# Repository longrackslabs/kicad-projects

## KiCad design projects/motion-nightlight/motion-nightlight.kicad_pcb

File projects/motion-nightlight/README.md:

# Motion Nightlight

Motion-activated nightlight built into a Nest Protect housing. ESP32 firmware, custom PCB, 3D printed enclosure and diffuser.

## Related files

| What | Where |
|------|-------|
| Design artifacts (DIYLC, FreeCAD, STLs, docs) | `Dropbox/Projects/Nest DIY Nightlight/` |
| Firmware | `~/src/platformio-projects/nest_night_light` |

---

## TODO

### PCB Changes

- [ ] Remote LDR — 2-pin JST header instead of THT so it can be positioned anywhere
- [ ] Right-angle JST on J1 and LED1
- [ ] Populate all MPNs in KiCad — needed for AI design review to catch pinout issues
- [ ] Fix C3 symbol — non-polarized ceramic
- [ ] Fix U2 lib_id — 74HC08 not 74LS08
- [ ] Add 47-100Ω resistor between U1 pin 10 and D1 anode
- [ ] Add Rev B silkscreen marking
- [ ] Fix RV1/RV2 3D model absolute paths

### Power

- [ ] Build single supply pigtail — splits one 5V to both V_LED+ and V_CONTROL on J1

### Enclosure

- [ ] Custom enclosure in FreeCAD — proper LED and LDR positioning
- [ ] Custom diffuser — Nest lens doesn't align with custom LED positions
- [ ] Access holes for RV1/RV2 trim pot adjustment

### Assembly

- [ ] First hot air reflow attempt with SAG-55 and Chipquik paste
- [ ] Build second board using incremental gate plan

### Stretch

- [ ] Replace discrete logic with ATtiny for more flexibility
- [ ] PWM dimming on Q2
- [ ] Battery level indicator

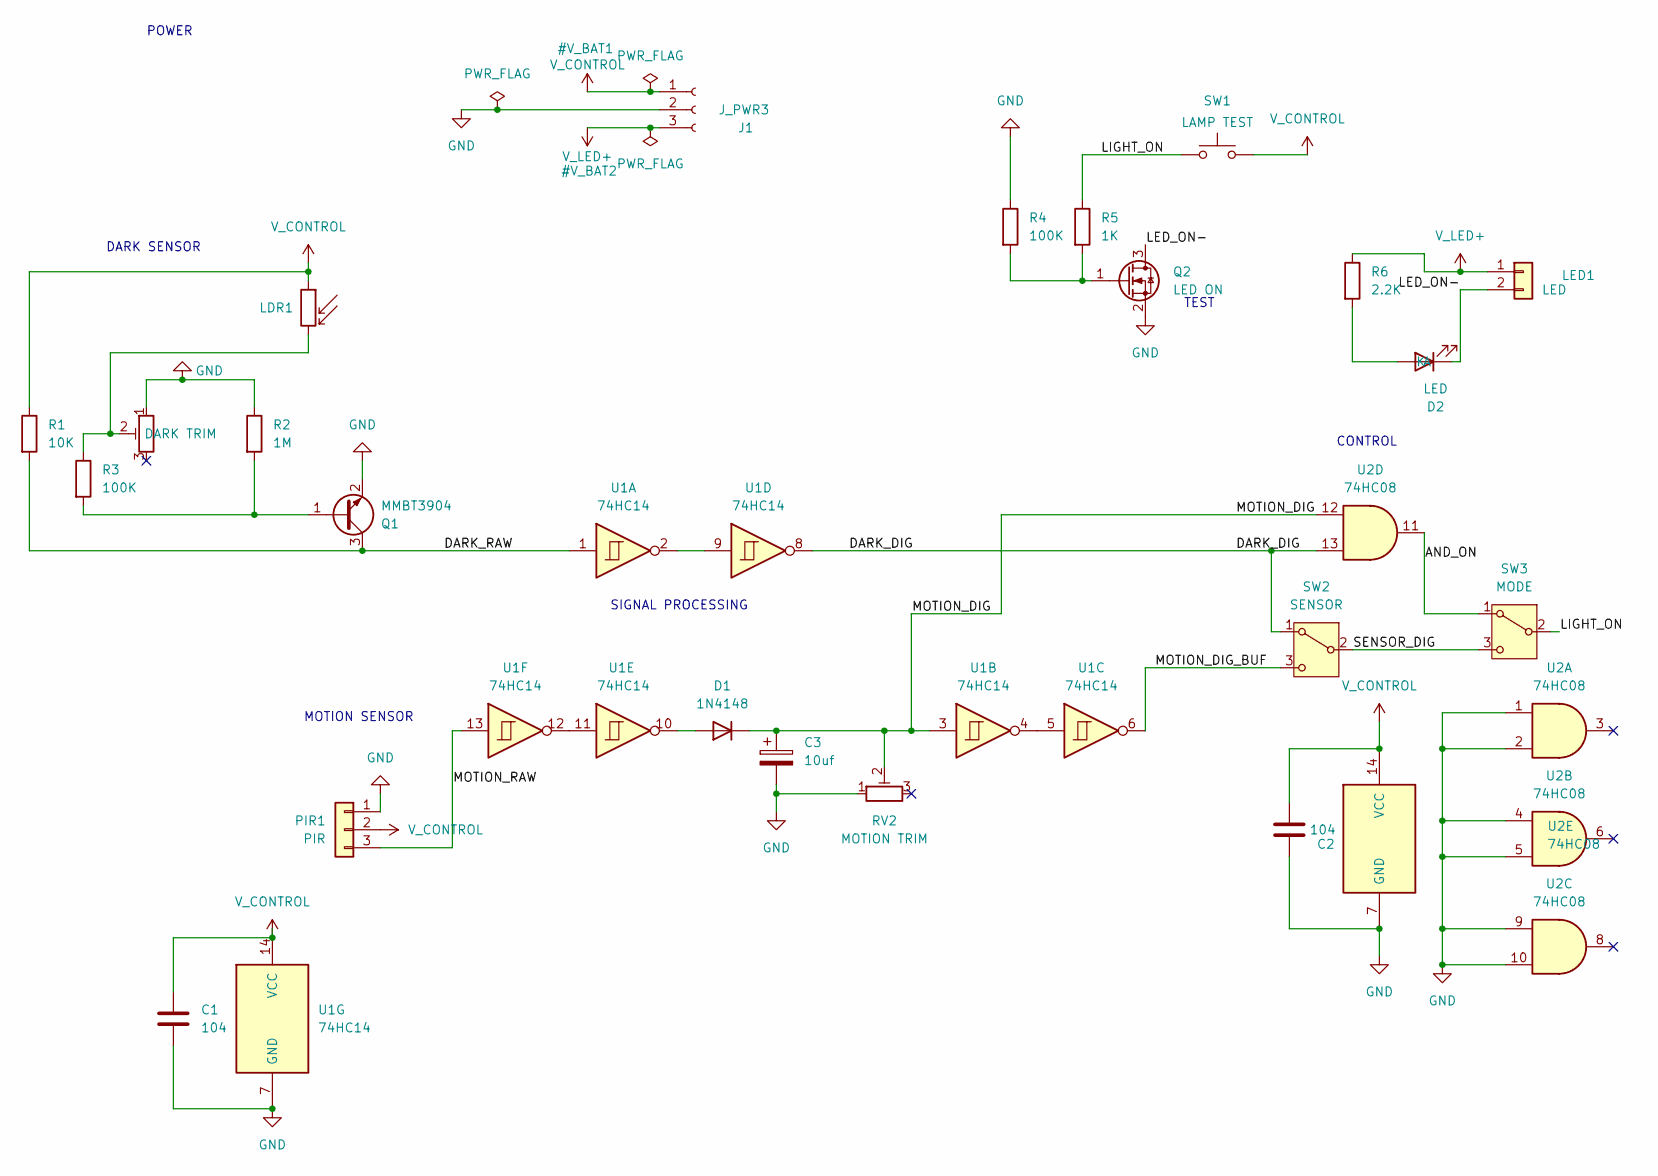
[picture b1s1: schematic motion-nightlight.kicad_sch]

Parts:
C1, C2: 104; C_0805_2012Metric_Pad1.18x1.45mm_HandSolder
C3: 10uf; C_0805_2012Metric_Pad1.18x1.45mm_HandSolder
D1: 1N4148; D_SOD-123
D2: LED; LED_0805_2012Metric
J1: J_PWR3; JST_XH_B3B-XH-A_1x03_P2.50mm_Vertical
LDR1: R_Photo; R_Axial_DIN0207_L6.3mm_D2.5mm_P7.62mm_Horizontal
LED1: LED; JST_XH_B2B-XH-A_1x02_P2.50mm_Vertical
PIR1: PIR; FanPinHeader_1x03_P2.54mm_Vertical
Q1: MMBT3904; SOT-23
Q2: LED ON; SOT-23
R1: 10K; R_0805_2012Metric_Pad1.20x1.40mm_HandSolder
R2: 1M; R_0805_2012Metric_Pad1.20x1.40mm_HandSolder
R3, R4: 100K; R_0805_2012Metric_Pad1.20x1.40mm_HandSolder
R5: 1K; R_0805_2012Metric_Pad1.20x1.40mm_HandSolder
R6: 2.2K; R_0805_2012Metric_Pad1.20x1.40mm_HandSolder
RV1: DARK TRIM; Potentiometer_Bourns_TC33X_Vertical
RV2: MOTION TRIM; Potentiometer_Bourns_TC33X_Vertical
SW1: LAMP TEST; SW_PUSH_6mm_H5mm
SW2: SENSOR; SW_SPDT_PCM12
SW3: MODE; SW_SPDT_PCM12
U1: 74HC14; SOIC-14_3.9x8.7mm_P1.27mm
U2: 74HC08; SOIC-14_3.9x8.7mm_P1.27mm

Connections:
/AND_ON: SW3.1 (A), U2.11
/DARK_DIG: SW2.1 (A), U1.8, U2.13
/DARK_RAW: Q1.3 (C), R1.2, U1.1
/LED_ON-: D2.1 (K), LED1.2, Q2.3 (D)
/LIGHT_ON: R5.1, SW1.1, SW3.2 (B)
/MOTION_DIG: C3.1, D1.1 (K), RV2.2, U1.3, U2.12
/MOTION_DIG_BUF: SW2.3 (C), U1.6
/MOTION_RAW: PIR1.3, U1.13
/SENSOR_DIG: SW2.2 (B), SW3.3 (C)
GND: C1.2, C2.2, C3.2, J1.2, PIR1.1, Q1.2 (E), Q2.2 (S), R2.1, R4.1, RV1.1, RV2.1, U1.7 (GND), U2.1, U2.2, U2.4, U2.5, U2.7 (GND), U2.9, U2.10
unnamed: D1.2 (A), U1.10
unnamed: D2.2 (A), R6.2
unnamed: LDR1.2, R3.1, RV1.2
unnamed: Q1.1 (B), R2.2, R3.2
unnamed: Q2.1 (G), R4.2, R5.2
unnamed: U1.2, U1.9
unnamed: U1.4, U1.5
unnamed: U1.11, U1.12
V_CONTROL: C1.1, C2.1, J1.1, LDR1.1, PIR1.2, R1.1, SW1.2, U1.14 (VCC), U2.14 (VCC)
V_LED+: J1.3, LED1.1, R6.1

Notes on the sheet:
POWER
DARK SENSOR
SIGNAL PROCESSING
MOTION SENSOR
CONTROL
TEST

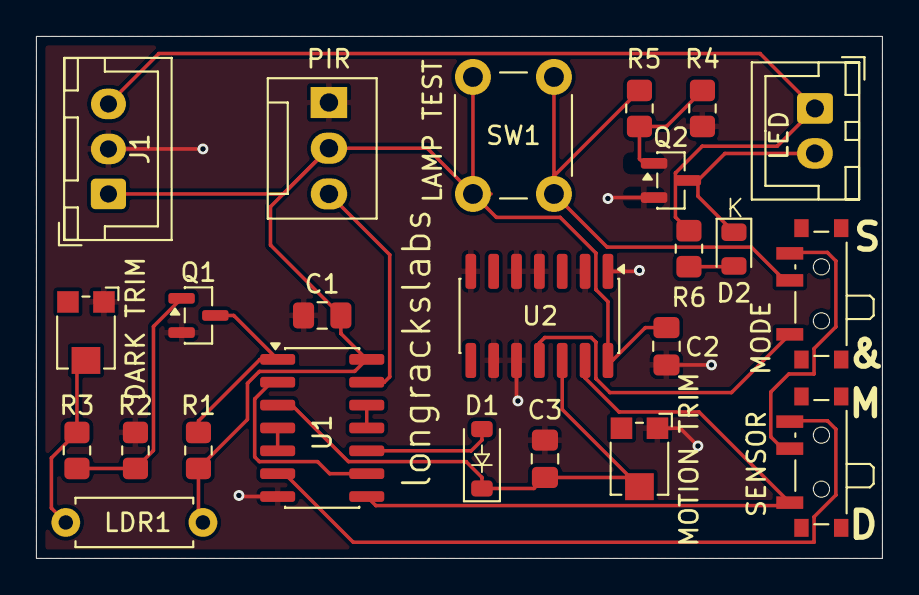
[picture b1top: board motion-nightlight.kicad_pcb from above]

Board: 2 copper layers, 47.0 x 29.0 mm, 24 parts (0 on the bottom side), 20 nets.

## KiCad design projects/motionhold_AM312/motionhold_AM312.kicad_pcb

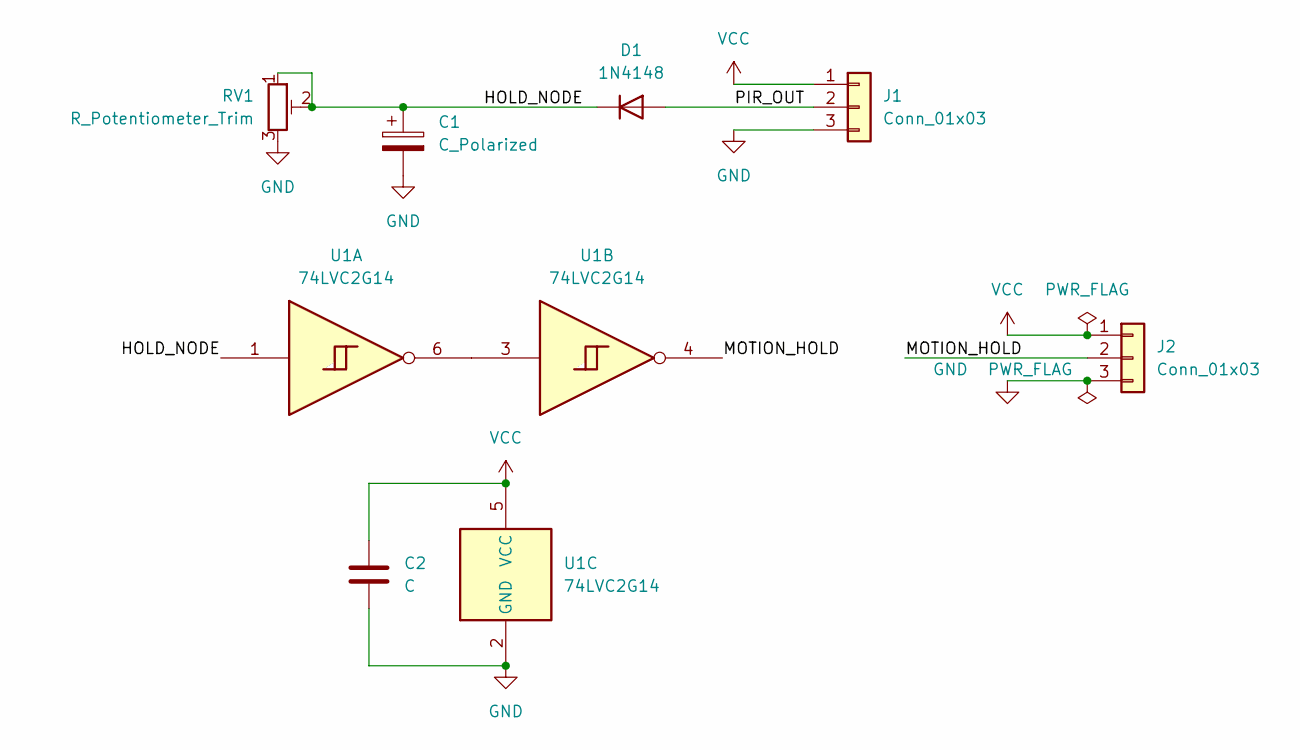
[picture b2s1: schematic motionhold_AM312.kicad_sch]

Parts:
C1: C_Polarized; C_0805_2012Metric_Pad1.18x1.45mm_HandSolder
C2: C; C_0805_2012Metric_Pad1.18x1.45mm_HandSolder
D1: 1N4148; D_SOD-123
J1, J2: Conn_01x03; PinHeader_1x03_P2.54mm_Vertical
RV1: R_Potentiometer_Trim; Potentiometer_Runtron_RM-065_Vertical
U1: 74LVC2G14; SOT-23-6

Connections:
/HOLD_NODE: C1.1, D1.1 (K), RV1.1, RV1.2, U1.1
/MOTION_HOLD: J2.2, U1.4
/PIR_OUT: D1.2 (A), J1.2
GND: C1.2, C2.2, J1.3, J2.3, RV1.3, U1.2 (GND)
unnamed: U1.3, U1.6
VCC: C2.1, J1.1, J2.1, U1.5 (VCC)

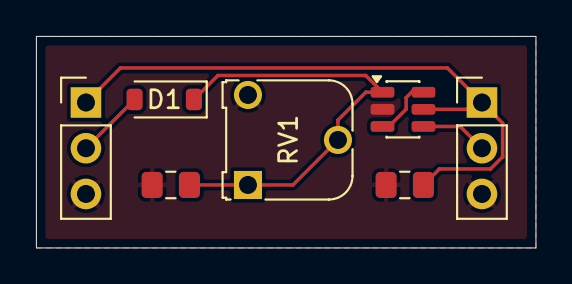
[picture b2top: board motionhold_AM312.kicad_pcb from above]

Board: 2 copper layers, 27.8 x 11.8 mm, 7 parts (0 on the bottom side), 6 nets.

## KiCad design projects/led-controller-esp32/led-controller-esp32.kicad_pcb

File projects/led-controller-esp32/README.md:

# LED Controller ESP32

General-purpose ESP32-based LED controller PCB.  
Compatible with **WLED**, **ESPHome (NeoPixelBus RMT)**, or **FastLED/Arduino**.  
Designed to drive 5 V addressable LEDs (WS2812B, SK6812, etc.).

---

## Project structure# LED Controller ESP32

General-purpose ESP32-based LED controller PCB.  
Compatible with **WLED**, **ESPHome (NeoPixelBus RMT)**, and **FastLED/Arduino**.  
Designed for 5 V addressable LEDs (WS2812B, SK6812, etc.).

## Project structure
led-controller-esp32/  
  led-controller-esp32.kicad_pro ← open this  
  led-controller-esp32.kicad_sch  
  led-controller-esp32.kicad_pcb  
  sym-lib-table (project-specific symbols)  
  fp-lib-table (project-specific footprints)  
  docs/  
  fabrication/ (gerbers/BOM/PNP; ignored by git)

## Libraries
- Project uses **relative paths** so it’s portable.
- Shared repos paths:
  - ../../libs/ → custom symbols & footprints
  - ../../step/ → 3D models

## How to open
1) Open `led-controller-esp32.kicad_pro` in KiCad.  
2) Edit schematic or PCB as usual.  
3) Generate fab outputs into `fabrication/` when ready to manufacture.

## Firmware options
- WLED (set LED pin to your chosen GPIO, e.g., 5)  
- ESPHome (NeoPixelBus, method: esp32_rmt)  
- FastLED (e.g., `#define DATA_PIN 5`)

## Notes / best practices
- Common ground between ESP32 and LED power.  
- 330 Ω series resistor on DATA; ≥1000 µF across 5 V/GND at LED input.  
- Avoid ESP32 boot-strap pins (0/2/12/15) for LED data.

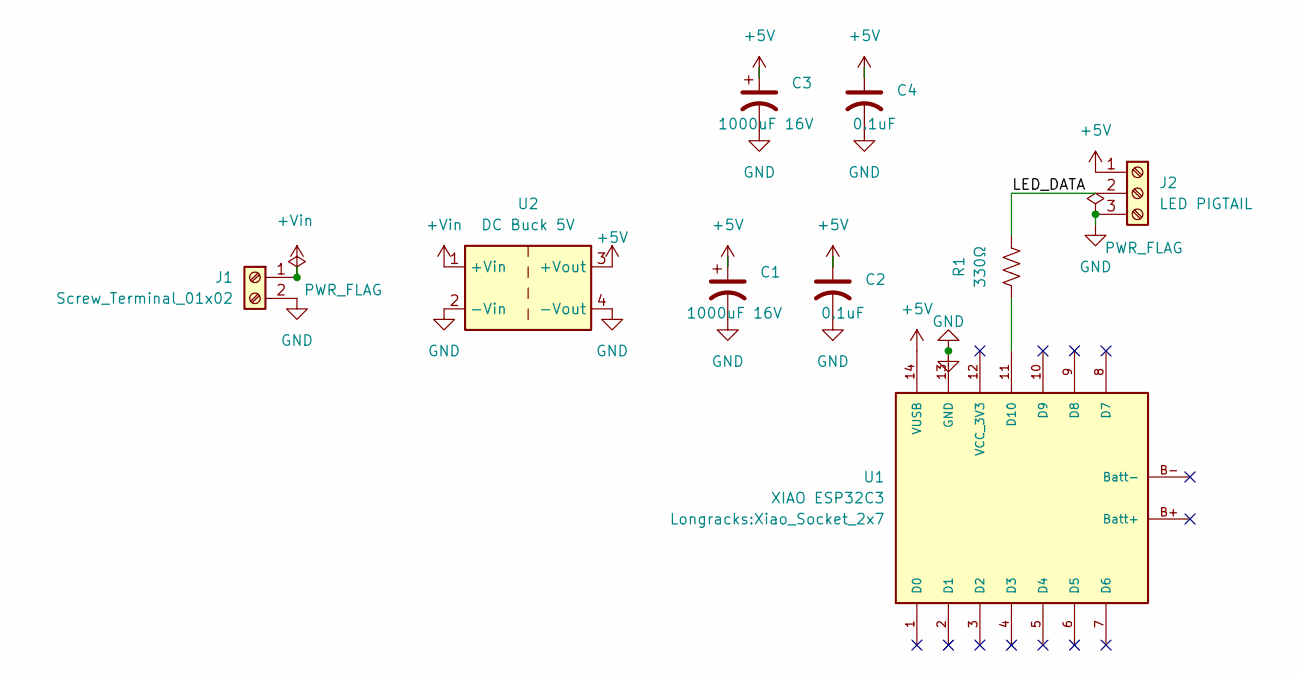
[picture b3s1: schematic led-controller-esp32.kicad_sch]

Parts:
C1, C3: 1000uF 16V; CP_Radial_D8.0mm_P3.50mm
C2, C4: 0.1uF; C_Disc_D5.0mm_W2.5mm_P5.00mm
J1: Screw_Terminal_01x02; TerminalBlock_Phoenix_MKDS-1,5-2-5.08_1x02_P5.08mm_Horizont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
J2: LED PIGTAIL; TerminalBlock_Phoenix_MKDS-1,5-3-5.08_1x03_P5.08mm_Horizont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
R1: 330Ω; R_Axial_DIN0207_L6.3mm_D2.5mm_P7.62mm_Horizontal
U1: XIAO ESP32C3; Xiao_Socket_2x7
U2: DC Buck 5V; DC_Buck_17x11mm

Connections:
+5V: C1.1, C2.1, C3.1, C4.1, J2.1, U1.14 (VUSB), U2.3 (+Vout)
+Vin: J1.1, U2.1 (+Vin)
/LED_DATA: J2.2, R1.2
GND: C1.2, C2.2, C3.2, C4.2, J1.2, J2.3, U1.13 (GND), U2.2 (-Vin), U2.4 (-Vout)
unnamed: R1.1, U1.11 (D10)

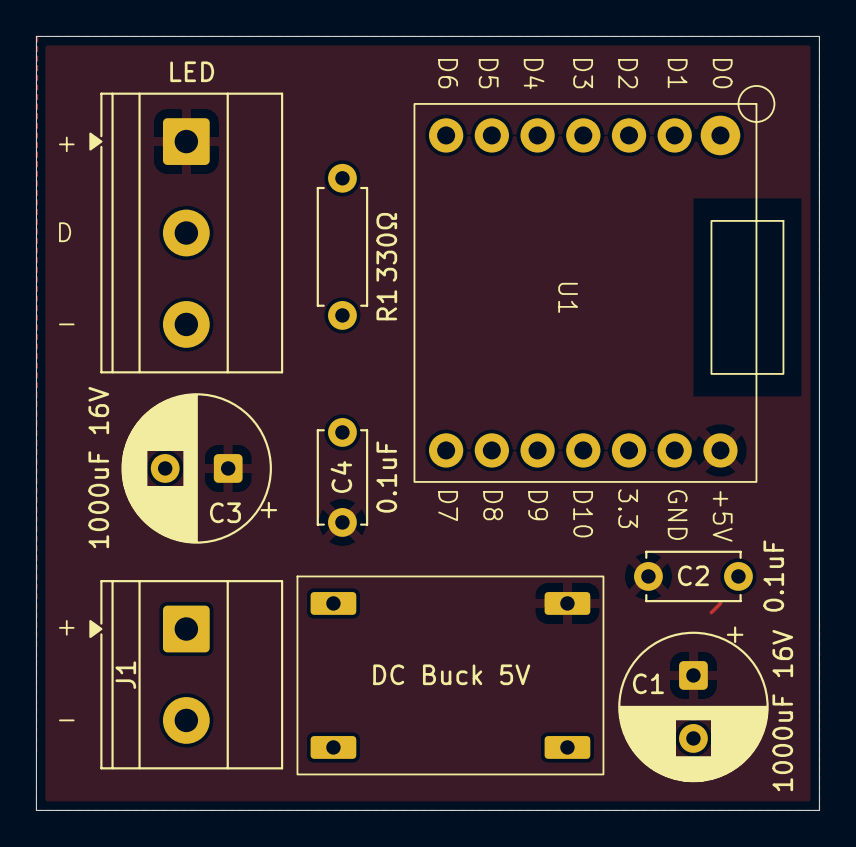
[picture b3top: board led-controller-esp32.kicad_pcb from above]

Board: 2 copper layers, 43.5 x 43.0 mm, 9 parts (0 on the bottom side), 5 nets.

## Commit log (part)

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2025-09-10 Initial structure: kicad-projects repo with libs + led-driver project wired to Longracks libs
2025-09-10 Add Longracks.pretty custom footprint library
2025-09-10 Add Longracks.pretty (XIAO_ESP32C3 footprint)
2025-09-10 Add Longracks.kicad_sym custom symbol library
2025-09-10 gitignore
2025-09-14 Rename led-driver project to led-controller-esp32
2025-09-14 add more kicad ignores
2025-09-14 xiao 2x7 socket
2025-09-14 basic README
2025-09-14 Initial commit of LED controller ESP32 KiCad project files
2025-09-14 use standard 2 screw terminal and other tidy ups
2025-09-14 label terminal blocks and other cleanups
2025-09-15 ignore lock files
2025-12-21 footprint for generic 3 pin slide switch
2025-12-21 Add motion-nightlight project
2025-12-21 Update slide switch description
2025-12-21 clean ERC and DRC
2025-12-21 layout tweaks for caps
2025-12-22 add motion off delay
2025-12-22 ignore auto saved files
2025-12-22 adding motion off delay
2025-12-22 fix up footprints and add step for trim pots
2026-01-01 final THT version
2026-01-02 SMD version ready for fab
2026-01-02 footprint for smd micro trimmer
